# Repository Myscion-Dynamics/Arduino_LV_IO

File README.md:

# Arduino LED Light Controller

This repo is for a simple LED light controller driven by an Arduino nano.
The lights are driven by a constant current LED driver with a range of 5mA - 200mA depending on the resistor installed.
The board can also be reconfigured as a generic io controller with a max current of 5A per channel.

The LED channels use a low side constant current driver and ifn the io configuration it uses a low side switch.

# Board Render

A board mount is included in this repo in the mechanical folder. This should be 3D printed with metric 3M threaded inserts installed.

# Manufactured board

# Software
Software for the LED configuration is included. It generates a random pattern of blinking lights.
The brightness is controlled in software and it monitores the input voltage to avoid overdischaring any batteries.
The software runs on an Arduino nano

# Configurations
For the Low side constant current source LED driver popuolate the following IC's 
U1, U2, U3, U4, U5, U6, U7, U8, U9. U10. U11, U12, U13, U14, U15, U15

For the low side switch configuration populate the following transistors
Q1, Q2, Q3, Q4, Q5, Q6, Q7, Q8, Q9, Q10, Q11, Q12, Q13, Q14, Q15, Q16 

Do not install the parts for both configurations at the same time.
It is posible to mix and match configurations are long as care is taken so only one of each is populated on each channel.

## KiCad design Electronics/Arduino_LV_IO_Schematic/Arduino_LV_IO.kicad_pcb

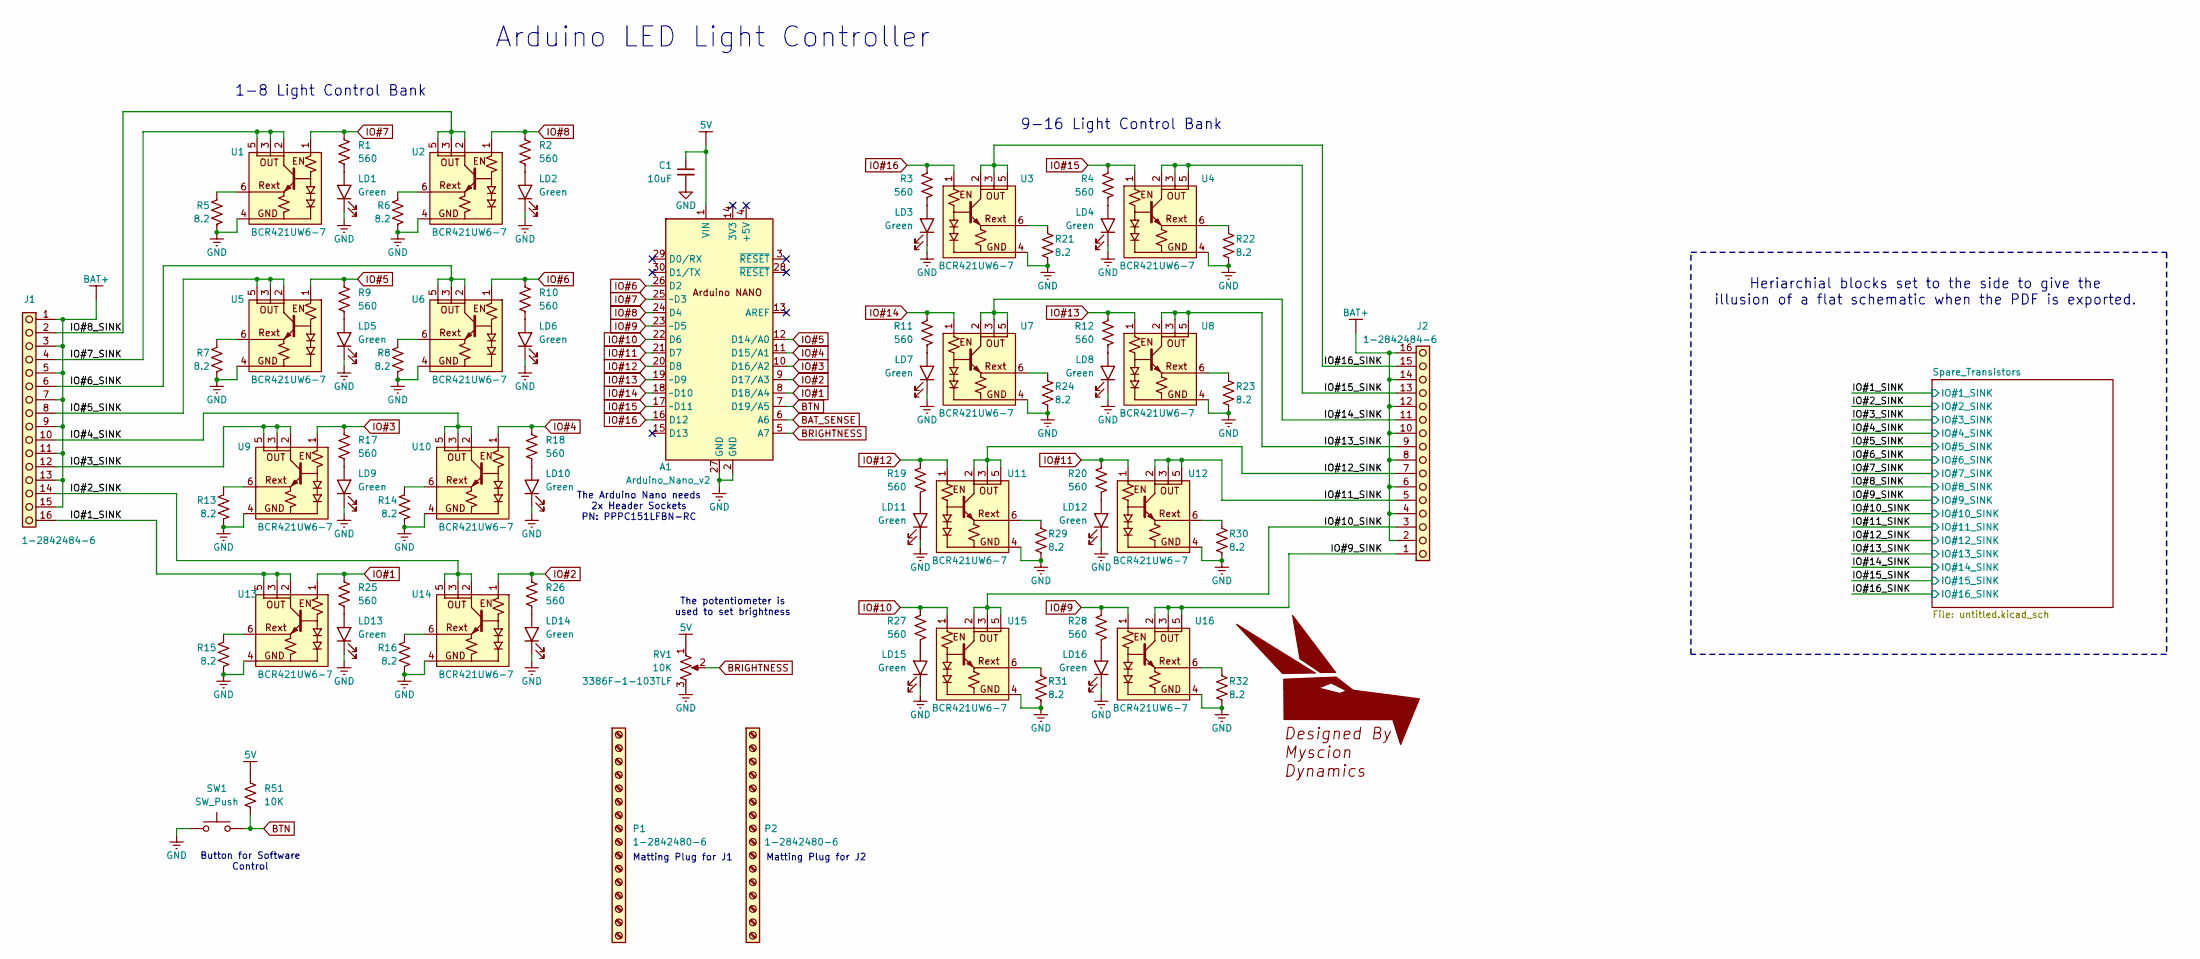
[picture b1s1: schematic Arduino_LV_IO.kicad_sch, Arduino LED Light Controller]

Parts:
A1: Arduino_Nano_v2; Arduino_Nano; MPN Arduino NANO
C1: 10uF; C_1210_3225Metric; Voltage 50V; Tolerance 10%; MPN CL32B106KBJNNNE
GL1: Myscion_Dynamics_Main
J1, J2: 1-2842484-6; TE_1x16_3.5mm_1-2842484-6; MPN 1-2842484-6
LD1, LD2, LD3, LD4, LD5, LD6, LD7, LD8, LD9, LD10, LD11, LD12, LD13, LD14, LD15, LD16: Green; LED_0603_1608Metric_Green_Cath_Dot; MPN HSME-C191
P1, P2: 1-2842480-6; MPN 1-2842480-6
R1, R2, R3, R4, R9, R10, R11, R12, R17, R18, R19, R20, R25, R26, R27, R28: 560; R_0603_1608Metric_Pad0.98x0.95mm_HandSolder; MPN RC0603FR-07560RL
R5, R6, R7, R8, R13, R14, R15, R16, R21, R22, R23, R24, R29, R30, R31, R32: 8.2; R_1206_3216Metric; MPN RMCF1206FT8R20
R51: 10K; R_0603_1608Metric_Pad0.98x0.95mm_HandSolder; MPN RC0603FR-0710KL
RV1: 10K; Potentiometer_Bourns_3386F_Vertical; MPN 3386F-1-103TLF
SW1: SW_Push; SW_PUSH-12mm_7mm_BLK; MPN TS14-1212-70-BK-160-SCR-D
U1, U2, U3, U4, U5, U6, U7, U8, U9, U10, U11, U12, U13, U14, U15, U16: SOT-23-6_Handsoldering; MPN BCR421UW6-7

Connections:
5V: A1.1 (VIN), C1.1, R51.2, RV1.1; also elsewhere on the board
/IO#1_SINK: J1.16, U13.2 (OUT), U13.3 (OUT), U13.5 (OUT); also elsewhere on the board
/IO#2_SINK: J1.14, U14.2 (OUT), U14.3 (OUT), U14.5 (OUT); also elsewhere on the board
/IO#3_SINK: J1.12, U9.2 (OUT), U9.3 (OUT), U9.5 (OUT); also elsewhere on the board
/IO#4_SINK: J1.10, U10.2 (OUT), U10.3 (OUT), U10.5 (OUT); also elsewhere on the board
/IO#5_SINK: J1.8, U5.2 (OUT), U5.3 (OUT), U5.5 (OUT); also elsewhere on the board
/IO#6_SINK: J1.6, U6.2 (OUT), U6.3 (OUT), U6.5 (OUT); also elsewhere on the board
/IO#7_SINK: J1.4, U1.2 (OUT), U1.3 (OUT), U1.5 (OUT); also elsewhere on the board
/IO#8_SINK: J1.2, U2.2 (OUT), U2.3 (OUT), U2.5 (OUT); also elsewhere on the board
/IO#9_SINK: J2.1, U16.2 (OUT), U16.3 (OUT), U16.5 (OUT); also elsewhere on the board
/IO#10_SINK: J2.3, U15.2 (OUT), U15.3 (OUT), U15.5 (OUT); also elsewhere on the board
/IO#11_SINK: J2.5, U12.2 (OUT), U12.3 (OUT), U12.5 (OUT); also elsewhere on the board
/IO#12_SINK: J2.7, U11.2 (OUT), U11.3 (OUT), U11.5 (OUT); also elsewhere on the board
/IO#13_SINK: J2.9, U8.2 (OUT), U8.3 (OUT), U8.5 (OUT); also elsewhere on the board
/IO#14_SINK: J2.11, U7.2 (OUT), U7.3 (OUT), U7.5 (OUT); also elsewhere on the board
/IO#15_SINK: J2.13, U4.2 (OUT), U4.3 (OUT), U4.5 (OUT); also elsewhere on the board
/IO#16_SINK: J2.15, U3.2 (OUT), U3.3 (OUT), U3.5 (OUT); also elsewhere on the board
BAT+: J1.1, J1.3, J1.5, J1.7, J1.9, J1.11, J1.13, J1.15, J2.2, J2.4, J2.6, J2.8, J2.10, J2.12, J2.14, J2.16; also elsewhere on the board
BAT_SENSE: A1.6 (A6); also elsewhere on the board
BRIGHTNESS: A1.5 (A7), RV1.2
BTN: A1.7 (D19/A5), R51.1, SW1.2
GND: A1.2 (GND), A1.27 (GND), C1.2, LD1.1 (K), LD2.1 (K), LD3.1 (K), LD4.1 (K), LD5.1 (K), LD6.1 (K), LD7.1 (K), LD8.1 (K), LD9.1 (K), LD10.1 (K), LD11.1 (K), LD12.1 (K), LD13.1 (K), LD14.1 (K), LD15.1 (K), LD16.1 (K), R5.2, R6.2, R7.2, R8.2, R13.2, R14.2, R15.2, R16.2, R21.2, R22.2, R23.2, R24.2, R29.2, R30.2, R31.2, R32.2, RV1.3, SW1.1, U1.4 (GND), U2.4 (GND), U3.4 (GND), U4.4 (GND), U5.4 (GND), U6.4 (GND), U7.4 (GND), U8.4 (GND), U9.4 (GND), U10.4 (GND), U11.4 (GND), U12.4 (GND), U13.4 (GND), U14.4 (GND), U15.4 (GND), U16.4 (GND); also elsewhere on the board
IO#1: A1.8 (D18/A4), R25.1, U13.1 (EN); also elsewhere on the board
IO#2: A1.9 (D17/A3), R26.1, U14.1 (EN); also elsewhere on the board
IO#3: A1.10 (D16/A2), R17.1, U9.1 (EN); also elsewhere on the board
IO#4: A1.11 (D15/A1), R18.1, U10.1 (EN); also elsewhere on the board
IO#5: A1.12 (D14/A0), R9.1, U5.1 (EN); also elsewhere on the board
IO#6: A1.26 (D2), R10.1, U6.1 (EN); also elsewhere on the board
IO#7: A1.25 (~D3), R1.1, U1.1 (EN); also elsewhere on the board
IO#8: A1.24 (D4), R2.1, U2.1 (EN); also elsewhere on the board
IO#9: A1.23 (~D5), R28.1, U16.1 (EN); also elsewhere on the board
IO#10: A1.22 (D6), R27.1, U15.1 (EN); also elsewhere on the board
IO#11: A1.21 (D7), R20.1, U12.1 (EN); also elsewhere on the board
IO#12: A1.20 (D8), R19.1, U11.1 (EN); also elsewhere on the board
IO#13: A1.19 (~D9), R12.1, U8.1 (EN); also elsewhere on the board
IO#14: A1.18 (~D10), R11.1, U7.1 (EN); also elsewhere on the board
IO#15: A1.17 (~D11), R4.1, U4.1 (EN); also elsewhere on the board
IO#16: A1.16 (D12), R3.1, U3.1 (EN); also elsewhere on the board
unnamed: LD1.2 (A), R1.2
unnamed: LD2.2 (A), R2.2
unnamed: LD3.2 (A), R3.2
unnamed: LD4.2 (A), R4.2
unnamed: LD5.2 (A), R9.2
unnamed: LD6.2 (A), R10.2
unnamed: LD7.2 (A), R11.2
unnamed: LD8.2 (A), R12.2
unnamed: LD9.2 (A), R17.2
unnamed: LD10.2 (A), R18.2
unnamed: LD11.2 (A), R19.2
unnamed: LD12.2 (A), R20.2
unnamed: LD13.2 (A), R25.2
unnamed: LD14.2 (A), R26.2
unnamed: LD15.2 (A), R27.2
unnamed: LD16.2 (A), R28.2
unnamed: R5.1, U1.6 (Rext)
unnamed: R6.1, U2.6 (Rext)
unnamed: R21.1, U3.6 (Rext)
unnamed: R22.1, U4.6 (Rext)
unnamed: R7.1, U5.6 (Rext)
unnamed: R8.1, U6.6 (Rext)
unnamed: R24.1, U7.6 (Rext)
unnamed: R23.1, U8.6 (Rext)
unnamed: R13.1, U9.6 (Rext)
unnamed: R14.1, U10.6 (Rext)
unnamed: R29.1, U11.6 (Rext)
unnamed: R30.1, U12.6 (Rext)
unnamed: R15.1, U13.6 (Rext)
unnamed: R16.1, U14.6 (Rext)
unnamed: R31.1, U15.6 (Rext)
unnamed: R32.1, U16.6 (Rext)

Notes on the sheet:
1-8 Light Control Bank
Button for Software Control
Matting Plug for J2
Heriarchial blocks set to the side to give the illusion of a flat schematic when the PDF is exported.
Arduino LED Light Controller
The Arduino Nano needs 2x Header Sockets PN: PPPC151LFBN-RC
9-16 Light Control Bank
The potentiometer is used to set brightness
Matting Plug for J1

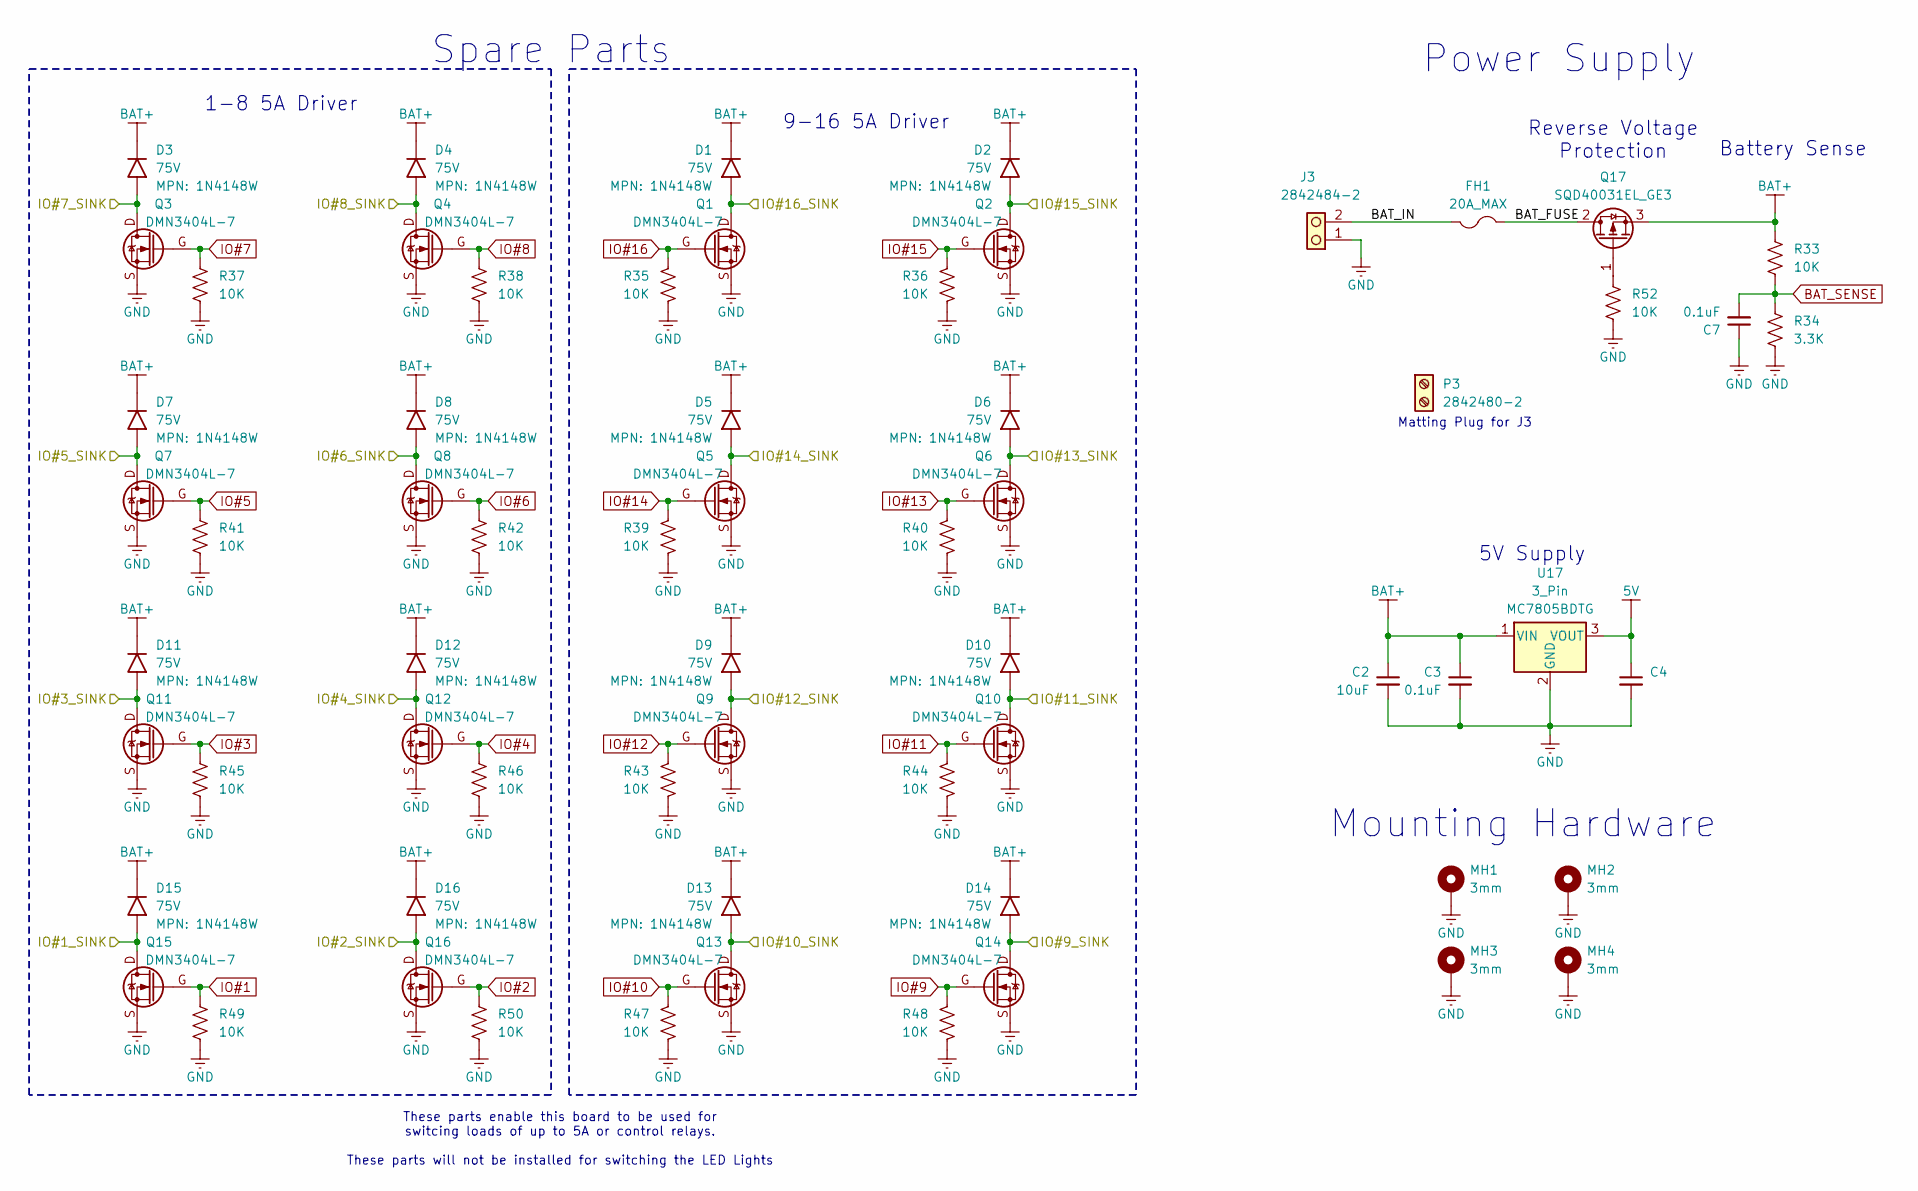
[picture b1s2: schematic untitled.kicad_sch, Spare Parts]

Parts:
C2: 10uF; C_1210_3225Metric; Voltage 50V; Tolerance 10%; MPN CL32B106KBJNNNE
C3, C4, C7: 0.1uF; C_0603_1608Metric_Pad1.08x0.95mm_HandSolder; Voltage 50V; Tolerance 10%; MPN CL10B104KB8NNNC
D1, D2, D3, D4, D5, D6, D7, D8, D9, D10, D11, D12, D13, D14, D15, D16: 75V; D_SOD-123; MPN 1N4148W
FH1: 20A_MAX; Wurth_696108003002; Voltage Rating 250V; MPN 696108003002
J3: 2842484-2; TE_1x16_3.5mm_2842484-2; MPN 2842484-2
MH1, MH2, MH3, MH4: 3mm; MountingHole_3.2mm_M3_Pad
P3: 2842480-2; MPN 2842480-2
Q1, Q2, Q3, Q4, Q5, Q6, Q7, Q8, Q9, Q10, Q11, Q12, Q13, Q14, Q15, Q16: DMN3404L-7; SOT-23-3_G-S-D; MPN DMN3404L-7
Q17: SQD40031EL_GE3; TO-252-2; MPN SQD40031EL_GE3
R33, R35, R36, R37, R38, R39, R40, R41, R42, R43, R44, R45, R46, R47, R48, R49, R50, R52: 10K; R_0603_1608Metric_Pad0.98x0.95mm_HandSolder; MPN RC0603FR-0710KL
R34: 3.3K; R_0603_1608Metric_Pad0.98x0.95mm_HandSolder; MPN RC0603FR-073K3L
U17: 3_Pin; TO-252-2; MPN MC7805BDTG

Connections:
5V: C4.1, U17.3 (VOUT); also elsewhere on the board
/IO#1_SINK: D15.2 (A), Q15.D; also elsewhere on the board
/IO#2_SINK: D16.2 (A), Q16.D; also elsewhere on the board
/IO#3_SINK: D11.2 (A), Q11.D; also elsewhere on the board
/IO#4_SINK: D12.2 (A), Q12.D; also elsewhere on the board
/IO#5_SINK: D7.2 (A), Q7.D; also elsewhere on the board
/IO#6_SINK: D8.2 (A), Q8.D; also elsewhere on the board
/IO#7_SINK: D3.2 (A), Q3.D; also elsewhere on the board
/IO#8_SINK: D4.2 (A), Q4.D; also elsewhere on the board
/IO#9_SINK: D14.2 (A), Q14.D; also elsewhere on the board
/IO#10_SINK: D13.2 (A), Q13.D; also elsewhere on the board
/IO#11_SINK: D10.2 (A), Q10.D; also elsewhere on the board
/IO#12_SINK: D9.2 (A), Q9.D; also elsewhere on the board
/IO#13_SINK: D6.2 (A), Q6.D; also elsewhere on the board
/IO#14_SINK: D5.2 (A), Q5.D; also elsewhere on the board
/IO#15_SINK: D2.2 (A), Q2.D; also elsewhere on the board
/IO#16_SINK: D1.2 (A), Q1.D; also elsewhere on the board
/Spare_Transistors/BAT_FUSE: FH1.2, Q17.2 (D)
/Spare_Transistors/BAT_IN: FH1.1, J3.2
BAT+: C2.1, C3.1, D1.1 (K), D2.1 (K), D3.1 (K), D4.1 (K), D5.1 (K), D6.1 (K), D7.1 (K), D8.1 (K), D9.1 (K), D10.1 (K), D11.1 (K), D12.1 (K), D13.1 (K), D14.1 (K), D15.1 (K), D16.1 (K), Q17.3 (S), R33.2, U17.1 (VIN); also elsewhere on the board
BAT_SENSE: C7.2, R33.1, R34.1; also elsewhere on the board
GND: C2.2, C3.2, C4.2, C7.1, J3.1, MH1.1, MH2.1, MH3.1, MH4.1, Q1.S, Q2.S, Q3.S, Q4.S, Q5.S, Q6.S, Q7.S, Q8.S, Q9.S, Q10.S, Q11.S, Q12.S, Q13.S, Q14.S, Q15.S, Q16.S, R34.2, R35.1, R36.1, R37.1, R38.1, R39.1, R40.1, R41.1, R42.1, R43.1, R44.1, R45.1, R46.1, R47.1, R48.1, R49.1, R50.1, R52.1, U17.2 (GND); also elsewhere on the board
IO#1: Q15.G, R49.2; also elsewhere on the board
IO#2: Q16.G, R50.2; also elsewhere on the board
IO#3: Q11.G, R45.2; also elsewhere on the board
IO#4: Q12.G, R46.2; also elsewhere on the board
IO#5: Q7.G, R41.2; also elsewhere on the board
IO#6: Q8.G, R42.2; also elsewhere on the board
IO#7: Q3.G, R37.2; also elsewhere on the board
IO#8: Q4.G, R38.2; also elsewhere on the board
IO#9: Q14.G, R48.2; also elsewhere on the board
IO#10: Q13.G, R47.2; also elsewhere on the board
IO#11: Q10.G, R44.2; also elsewhere on the board
IO#12: Q9.G, R43.2; also elsewhere on the board
IO#13: Q6.G, R40.2; also elsewhere on the board
IO#14: Q5.G, R39.2; also elsewhere on the board
IO#15: Q2.G, R36.2; also elsewhere on the board
IO#16: Q1.G, R35.2; also elsewhere on the board
unnamed: Q17.1 (G), R52.2

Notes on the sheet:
Mounting Hardware
Spare Parts
These parts enable this board to be used for switcing loads of up to 5A or control relays. These parts will not be installed for switching the LED Lights
Power Supply
1-8 5A Driver
5V Supply
Reverse Voltage Protection
9-16 5A Driver
Battery Sense
Matting Plug for J3

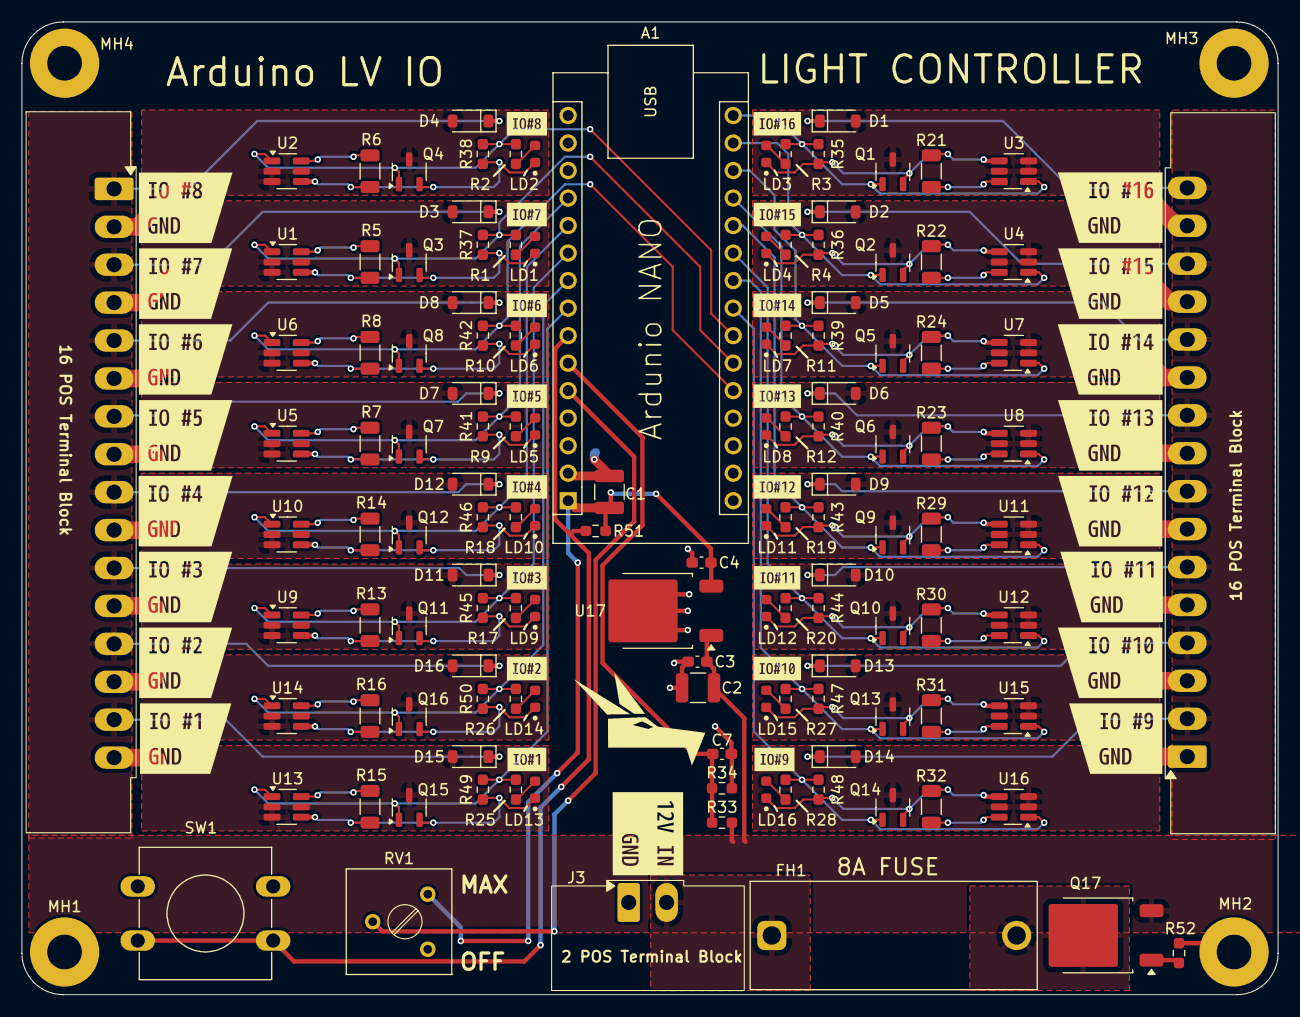
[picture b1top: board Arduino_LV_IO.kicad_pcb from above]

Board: 2 copper layers, 116.0 x 89.8 mm, 168 parts (0 on the bottom side), 73 nets.

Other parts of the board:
kibuzzard-68815A57: G***; kibuzzard-68815A57
kibuzzard-68816CB7: G***; kibuzzard-68816CB7
kibuzzard-68818BC9: G***; kibuzzard-68818BC9
kibuzzard-68818BD0: G***; kibuzzard-68818BD0
kibuzzard-68818BD6: G***; kibuzzard-68818BD6
kibuzzard-68818BDE: G***; kibuzzard-68818BDE
kibuzzard-68818BE4: G***; kibuzzard-68818BE4
kibuzzard-68818BEC: G***; kibuzzard-68818BEC
kibuzzard-68818BF4: G***; kibuzzard-68818BF4
kibuzzard-68818BFA: G***; kibuzzard-68818BFA
kibuzzard-68818C0A: G***; kibuzzard-68818C0A
kibuzzard-68818C1C: G***; kibuzzard-68818C1C
kibuzzard-68818C02: G***; kibuzzard-68818C02
kibuzzard-68818C2E: G***; kibuzzard-68818C2E
kibuzzard-68818C16: G***; kibuzzard-68818C16
kibuzzard-68818C23: G***; kibuzzard-68818C23
kibuzzard-68818C28: G***; kibuzzard-68818C28
kibuzzard-68818C34: G***; kibuzzard-68818C34
kibuzzard-688053C9: G***; kibuzzard-688053C9
kibuzzard-688160B8: G***; kibuzzard-688160B8
kibuzzard-688164DF: G***; kibuzzard-688164DF
kibuzzard-688165F4: G***; kibuzzard-688165F4
kibuzzard-688184E6: G***; kibuzzard-688184E6
kibuzzard-6881677E: G***; kibuzzard-6881677E
kibuzzard-6881678F: G***; kibuzzard-6881678F
kibuzzard-6881766C: G***; kibuzzard-6881766C
kibuzzard-6881854C: G***; kibuzzard-6881854C
kibuzzard-6881860D: G***; kibuzzard-6881860D
kibuzzard-68816783: G***; kibuzzard-68816783
kibuzzard-68816789: G***; kibuzzard-68816789
kibuzzard-68818591: G***; kibuzzard-68818591
kibuzzard-68818672: G***; kibuzzard-68818672
kibuzzard-68818677: G***; kibuzzard-68818677

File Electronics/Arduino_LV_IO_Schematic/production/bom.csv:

Designator,Footprint,Quantity,Value,LCSC Part #
A1,Arduino_Nano,1,Arduino_Nano_v2,Arduino NANO
"C1, C2",1210,2,10uF,CL32B106KBJNNNE
"C3, C4, C7",0603,3,0.1uF,CL10B104KB8NNNC
"D1, D10, D11, D12, D13, D14, D15, D16, D2, D3, D4, D5, D6, D7, D8, D9",D_SOD-123,16,75V,1N4148W
FH1,Wurth_696108003002,1,20A_MAX,696108003002
"J1, J2",TE_1x16_3.5mm_1-2842484-6,2,1-2842484-6,1-2842484-6
J3,TE_1x16_3.5mm_2842484-2,1,2842484-2,2842484-2
"LD1, LD10, LD11, LD12, LD13, LD14, LD15, LD16, LD2, LD3, LD4, LD5, LD6, LD7, LD8, LD9",0603,16,Green,HSME-C191
"MH1, MH4",MountingHole_3.2mm_M3_Pad,2,3mm,
"Q1, Q10, Q11, Q12, Q13, Q14, Q15, Q16, Q2, Q3, Q4, Q5, Q6, Q7, Q8, Q9",SOT-23-3_G-S-D,16,DMN3404L-7,DMN3404L-7
Q17,TO-252-2,1,SQD40031EL_GE3,SQD40031EL_GE3
"R1, R10, R11, R12, R17, R18, R19, R2, R20, R25, R26, R27, R28, R3, R4, R9",0603,16,560,RC0603FR-07560RL
"R13, R14, R15, R16, R21, R22, R23, R24, R29, R30, R31, R32, R5, R6, R7, R8",1206,16,8.2,RMCF1206FT8R20
"R33, R35, R36, R37, R38, R39, R40, R41, R42, R43, R44, R45, R46, R47, R48, R49, R50, R51, R52",0603,19,10K,RC0603FR-0710KL
R34,0603,1,3.3K,RC0603FR-073K3L
RV1,Potentiometer_Bourns_3386F_Vertical,1,10K,3386F-1-103TLF
SW1,SW_PUSH-12mm_7mm_BLK,1,SW_Push,TS14-1212-70-BK-160-SCR-D
"U1, U10, U11, U12, U13, U14, U15, U16, U2, U3, U4, U5, U6, U7, U8, U9",SOT-23-6_Handsoldering,16,~,BCR421UW6-7
U17,TO-252-2,1,3_Pin,MC7805BDTG

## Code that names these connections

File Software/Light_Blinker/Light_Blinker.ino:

// Code to control the Arduino LED light blinker
// This code is for the board in it's LED driver configuration
// This code toggles the IO outputs to blink the lights in a random pattern
// The random pattern is generated at the start of the program
// The code reads an analog input that is used to control how bright the LED's are
// The LED brightness is controlled by a software PWM driver
// A button can be used to enable and disable the LED lights
// If the code is not working make sure the potentiometer is set to max and try pressing the button

// These integers are used to asign the pin number to each pin name, this is done to make the code easier to read
const int io1 = 18;  // PC4
const int io2 = 17;  // PC3
const int io3 = 16;  // PC2
const int io4 = 15;  // PC1
const int io5 = 14;  // PC0
const int io6 = 2;   // PD2
const int io7 = 3;   // PD3
const int io8 = 4;   // PD4
const int io9 = 5;   // PD5
const int io10 = 6;  // PD6
const int io11 = 7;  // PD7
const int io12 = 8;  // PB0
const int io13 = 9;  // PB1
const int io14 = 10; // PB2
const int io15 = 11; // PB3
const int io16 = 12; // PB4
const int btn = 19;  // PC5
const int pot_pin = A7;
const int bat_sense_pin = A6;


//These variables can be changed to alter  performance
int threashold = 127; // Range 0-254, Used to compare to random numbers to determine if an LED is on, higher turs on more LED's
int cycleTime = 4000; //Milisceonds per cycle

// Do not change these variables
#define SQLENGTH 800 // How many steps in the sequence, if you go higher than 800 the arduino may run out of ram
uint16_t squence[SQLENGTH]; // Array to hold the seqence data
bool enabled = true; //Set to disabled if battery gets too low

void generateSequence(){// Generate a sequence of random numbers ahead of time
  for(int i = 0; i < SQLENGTH - 1; i++){ // This loops through each item in the array
    squence[i] = 0; // zero out the sequence if this is being re ran a 2nd time
    for(int ran_i = 0; ran_i < 16; ran_i++){ // This loops through the 16 bits on each item in the array
      int ran = random(0, 255);
      if (ran > threashold){ // The random number is between 0 and 255, the threashold can be used to bias the numbers on or off
        squence[i] = squence[i] | (1 << ran_i); // Shift 1 into the position that was just evaluated and store it in the sequence 
      }
    }
  }
}

// IO Range PC0-PC4, PB0-PB4, PD2-PD7
// Button = PC5
void writeSeqeunce(uint16_t data, float brightness, int wait){
  // This fuction takes in "data" and displays it at the speficied "brightness", the funcation uses "wait" to determine how long it should wait
  int ton = 1000 * brightness; // Calculate time on in micro seconds (us)
  int toff = 1000 * (1 - brightness); // Calcuate time off in us
  if (toff < 0) toff = 0; // Make sure time off never goes negative, due to how the potentiometer is sampled brightes can be higher than 100. This is a bit of a clumsy fix


  // For the sake of speed the PORT registers are used instead of the build in arduino digital write
  // Digital write is slow and this operation is much faster. For manual pin control there are three ports. PORTB, PORTC and PORTD
  // Each port has 3 registers, PORTB, PINB, DDRB, the registers control if the pin is on/off, input/output
  uint8_t PB = (data & 0b11111) | (PORTB & 0b11100000);
  uint8_t PC = ((data >> 5) & 0b11111) | (PORTC & 0b11100000);
  uint8_t PD = ((data >> 8) & 0b11111100) | (PORTD & 0b00000011);

  // This is the software brightness function, each cycle is 1 miliscond (ms), the delayMicroseconds command is used for higher accuracy
  for(int i = 0; i < wait; i++){
    PORTB = PB;
    PORTC = PC;
    PORTD = PD;
    delayMicroseconds(ton);

    PORTB &= 0b11100000;
    PORTC &= 0b11100000;
    PORTD &= 0b00000011;
    delayMicroseconds(toff);

    // Check if the button is pressed to turn the LED's off
    uint8_t btn_reg = PINC & 0b00100000;
    if(btn_reg == 0){
      enabled = false;
      delay(2000);
      break;
    }
  }

}

#define BAT_LOW 625 // Cut off at 10.5V, 2.06V on the divider
void checkBattery(){ // This function  checks if the battery is low
  int batt_reading = analogRead(bat_sense_pin);
  
  if(batt_reading < BAT_LOW){ // If the battery is low turn off all the lights
    uint8_t PB = (0b11111) | (PORTB & 0b11100000);
    uint8_t PC = (0b11111) | (PORTC & 0b11100000);
    uint8_t PD = (0b11111100) | (PORTD & 0b00000011);

    for(uint8_t i = 0; i < 5; i++){ // Flash the lights a few times
      PORTB = PB;
      PORTC = PC;
      PORTD = PD;
      delay(300);

      PORTB &= 0b11100000;
      PORTC &= 0b11100000;
      PORTD &= 0b00000011;
      delay(300);
    }

    while(true){ // Keep the lights off but flash them is the user preses the button
      uint8_t btn_reg = PINC & 0b00100000;
      if(btn_reg == 0){
        for(uint8_t i = 0; i < 5; i++){
          PORTB = PB;
          PORTC = PC;
          PORTD = PD;
          delay(300);

          PORTB &= 0b11100000;
          PORTC &= 0b11100000;
          PORTD &= 0b00000011;
          delay(300);
        }
      }
    }
  }
}

// The setup code runs once at the start
void setup() {
  // Configure the output mode of all the pins
  pinMode(io1, OUTPUT);
  pinMode(io2, OUTPUT);
  pinMode(io3, OUTPUT);
  pinMode(io4, OUTPUT);
  pinMode(io5, OUTPUT);
  pinMode(io6, OUTPUT);
  pinMode(io7, OUTPUT);
  pinMode(io8, OUTPUT);
  pinMode(io9, OUTPUT);
  pinMode(io10, OUTPUT);
  pinMode(io11, OUTPUT);
  pinMode(io12, OUTPUT);
  pinMode(io13, OUTPUT);
  pinMode(io14, OUTPUT);
  pinMode(io15, OUTPUT);
  pinMode(io16, OUTPUT);

  // Generate the sequence
  generateSequence();

  // Set the data direction registers. This may not be needed due to the pinMode commands 
  DDRB |= 0b00011111;
  DDRC |= 0b00011111;
  DDRD |= 0b11111100;
}

int sequencePos = 0;
int pot_reading = 0;
float brightness = 0;

// This loop runs continously
void loop() {
  sequencePos++;
  if(sequencePos > SQLENGTH - 1){ // Reset the seqence if it reaches the end
    sequencePos = 0;
  }

  // Read the analog pot and use it to set the brightness value
  pot_reading = analogRead(pot_pin);
  brightness = pot_reading/870.0;
  
  // If enabled run the next step of the seqence
  if(enabled){
    writeSeqeunce(squence[sequencePos], brightness, cycleTime);
  }else{
    for(int i = 0; i < 1000; i++){

      // Check if the button is pressed to turn the LED's back on
      uint8_t btn_reg = PINC & 0b00100000;
      if(btn_reg == 0){
        enabled = true;
        delay(5);
        while(btn_reg == 0){
          btn_reg = PINC & 0b00100000;
        }
        delay(5);

        break;
      }
      delayMicroseconds(1000);
    }
  }

  // Check the battery once per iteration
  checkBattery();

}

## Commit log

2025-08-17 add files
